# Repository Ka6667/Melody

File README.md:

# Melody

## Table of Contents
* [What is MELODY?](#what-is-melody)
* [Why did I build it?](#why-did-i-build-it)
* [How to use MELODY](#how-to-use-melody)
* [Schematics](#schematics)
* [PCB Design](#pcb-design)
* [3D Model](#3d-model)
* [BOM](#bom)

## What is MELODY?
MELODY is a fun, easy to use mini game console featuring five different panda-themed games! The design is incredibly straightforward to assemble, and it even attaches right to your keychain so you can take it anywhere.

## Why did I build it?
my best friend, Melody, asked me to build something for her. so I decided to make a mini game console for her which includes many mini-games. 

## How to use MELODY?
Bringing MELODY to life is easy! Just print the PCB, solder the components, and 3D print the case. Once your parts are ready, assemble everything using M2 screws and attach it right to your keychain. From there, the firmware is incredibly straightforward—just pick one of the five games and start playing!

## Schematics

## PCB Design

## 3D Model

## BOM

| Part | Amount | Price | Link |
| :--- | :---: | :---: | :--- |
| XIAO rp2040 | 1 | $5.40 | [Temu Link](https://temu.com/ul/kuiper/un9.html) |
| TFT LCD Display Module | 1 | $7.34 | [Amazon Link](https://www.amazon.eg/-/en/TFT-Display-Module-Interface-Inch/dp/B0CJ851LDT/) |
| buzzer | 1 | $0.1 | [Temu Link](https://www.temu.com/ul/kuiper/un9.html) |
| LIPO-Battery | 1 | $1.10 | [Makers Electronics Link](https://makerselectronics.com/product/rechargeable-400925-lipo-battery/) |
| Screws | 4 | $1.50 | [Temu Link](https://www.temu.com/ul/kuiper/un9.html) |
| joystick module | 1 | $1.34 | [Amazon Link](https://www.amazon.eg/-/en/Generic-414999-483-Potentiometer-10K-Ohm/dp/B091DX3483/) |
| PCB | 1 | $2.00 | [JLCPCB Link](https://cart.jlcpcb.com) |
| **Total** | | **$18.78** <br>*(shipping not included)* | |

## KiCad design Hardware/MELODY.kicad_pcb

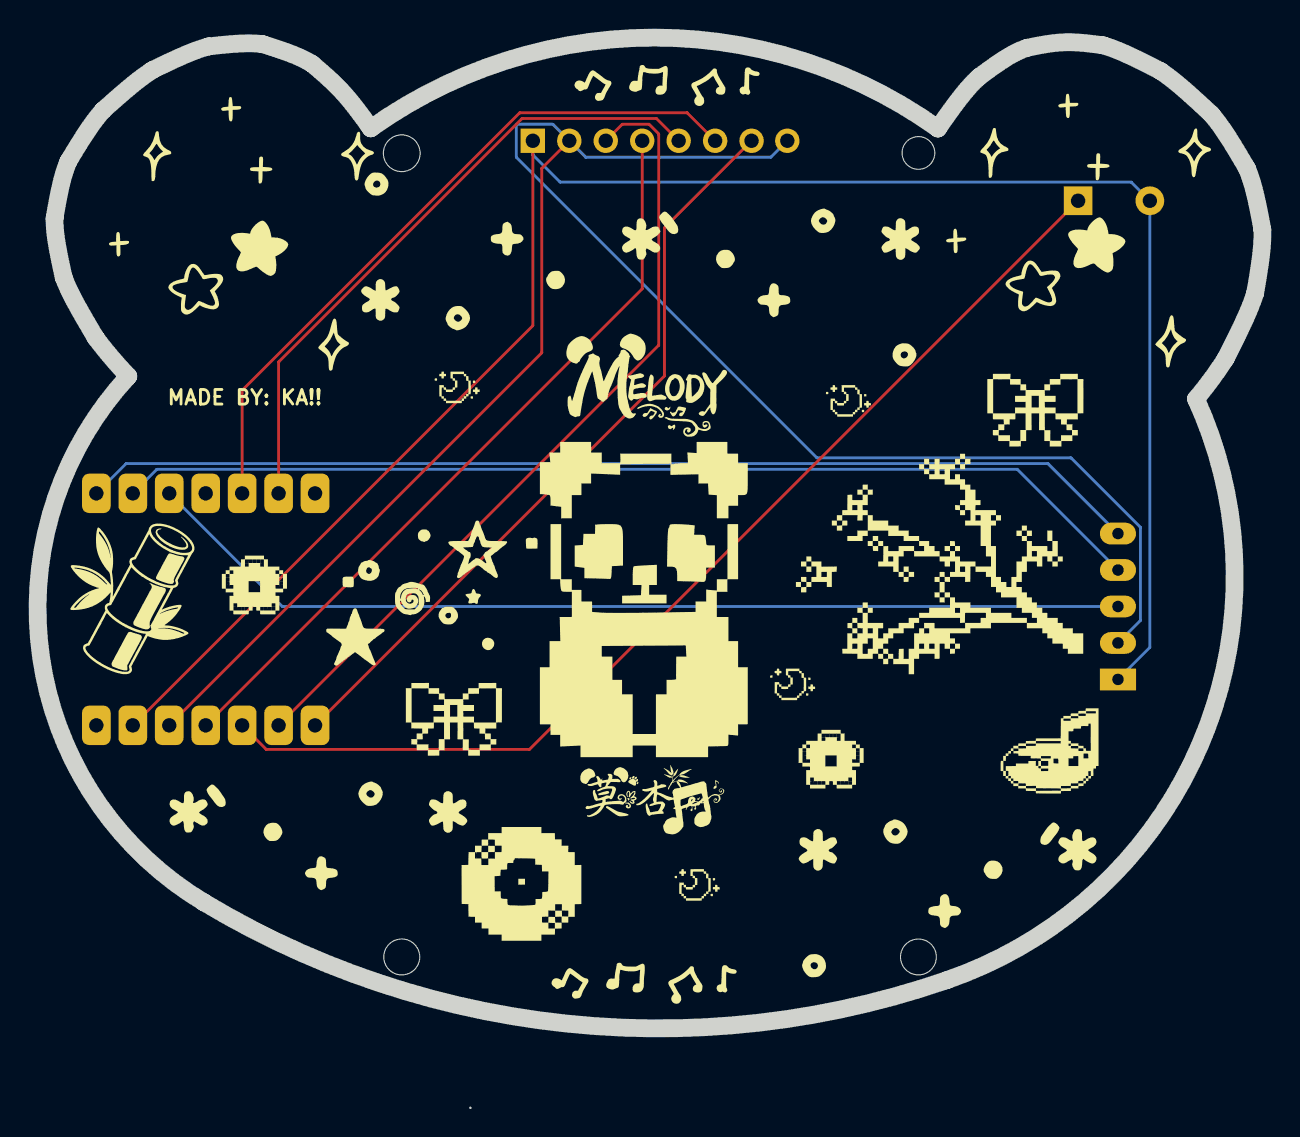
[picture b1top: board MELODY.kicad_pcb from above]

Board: 2 copper layers, 85.3 x 74.6 mm, 4 parts (1 on the bottom side), 11 nets.

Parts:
AFF1: Joystick-w-sw; 7SegmentLED_LTS6760_LTS6780
BZe1: Buzzer; Buzzer_TDK_PS1240P02BT_D12.2mm_H6.5mm
U2: XIAO-RP2040-SMD
Ue1: ST7735; ST7789_1.3_240x240_LCD_Module

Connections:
+3.3V: AFF1.2 (VCC), U2.12 (3V3_OUT), Ue1.2 (VCC), Ue1.7 (CS)
/A0: AFF1.5 (SW), U2.1 (D0)
/A1: AFF1.4 (VRy), U2.2 (D1)
/A2: AFF1.3 (VRx), U2.3 (D2)
/D4: U2.5 (D4), Ue1.6 (DC)
/D5: U2.6 (D5), Ue1.5 (RES)
/D7: U2.8 (D7), Ue1.7 (CS)
/D8: U2.9 (D8), Ue1.3 (SCL)
/D9: BZe1.1 (+), U2.10 (D9)
/D10: U2.11 (D10), Ue1.4 (SDA)
GND: AFF1.1 (GND), BZe1.2 (-), U2.13 (GND), Ue1.1 (GND)
